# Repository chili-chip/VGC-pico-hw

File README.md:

# VGC-pico-hw
KiCad harware project for VGC-0 based on pico and esp32

Brain of the operation is RP2350, while ESP8684 is used for WiFi and extra GPIO.

Input system consists of 6 regular buttons, 2 system buttons and an encoder wheel.

Meow :3

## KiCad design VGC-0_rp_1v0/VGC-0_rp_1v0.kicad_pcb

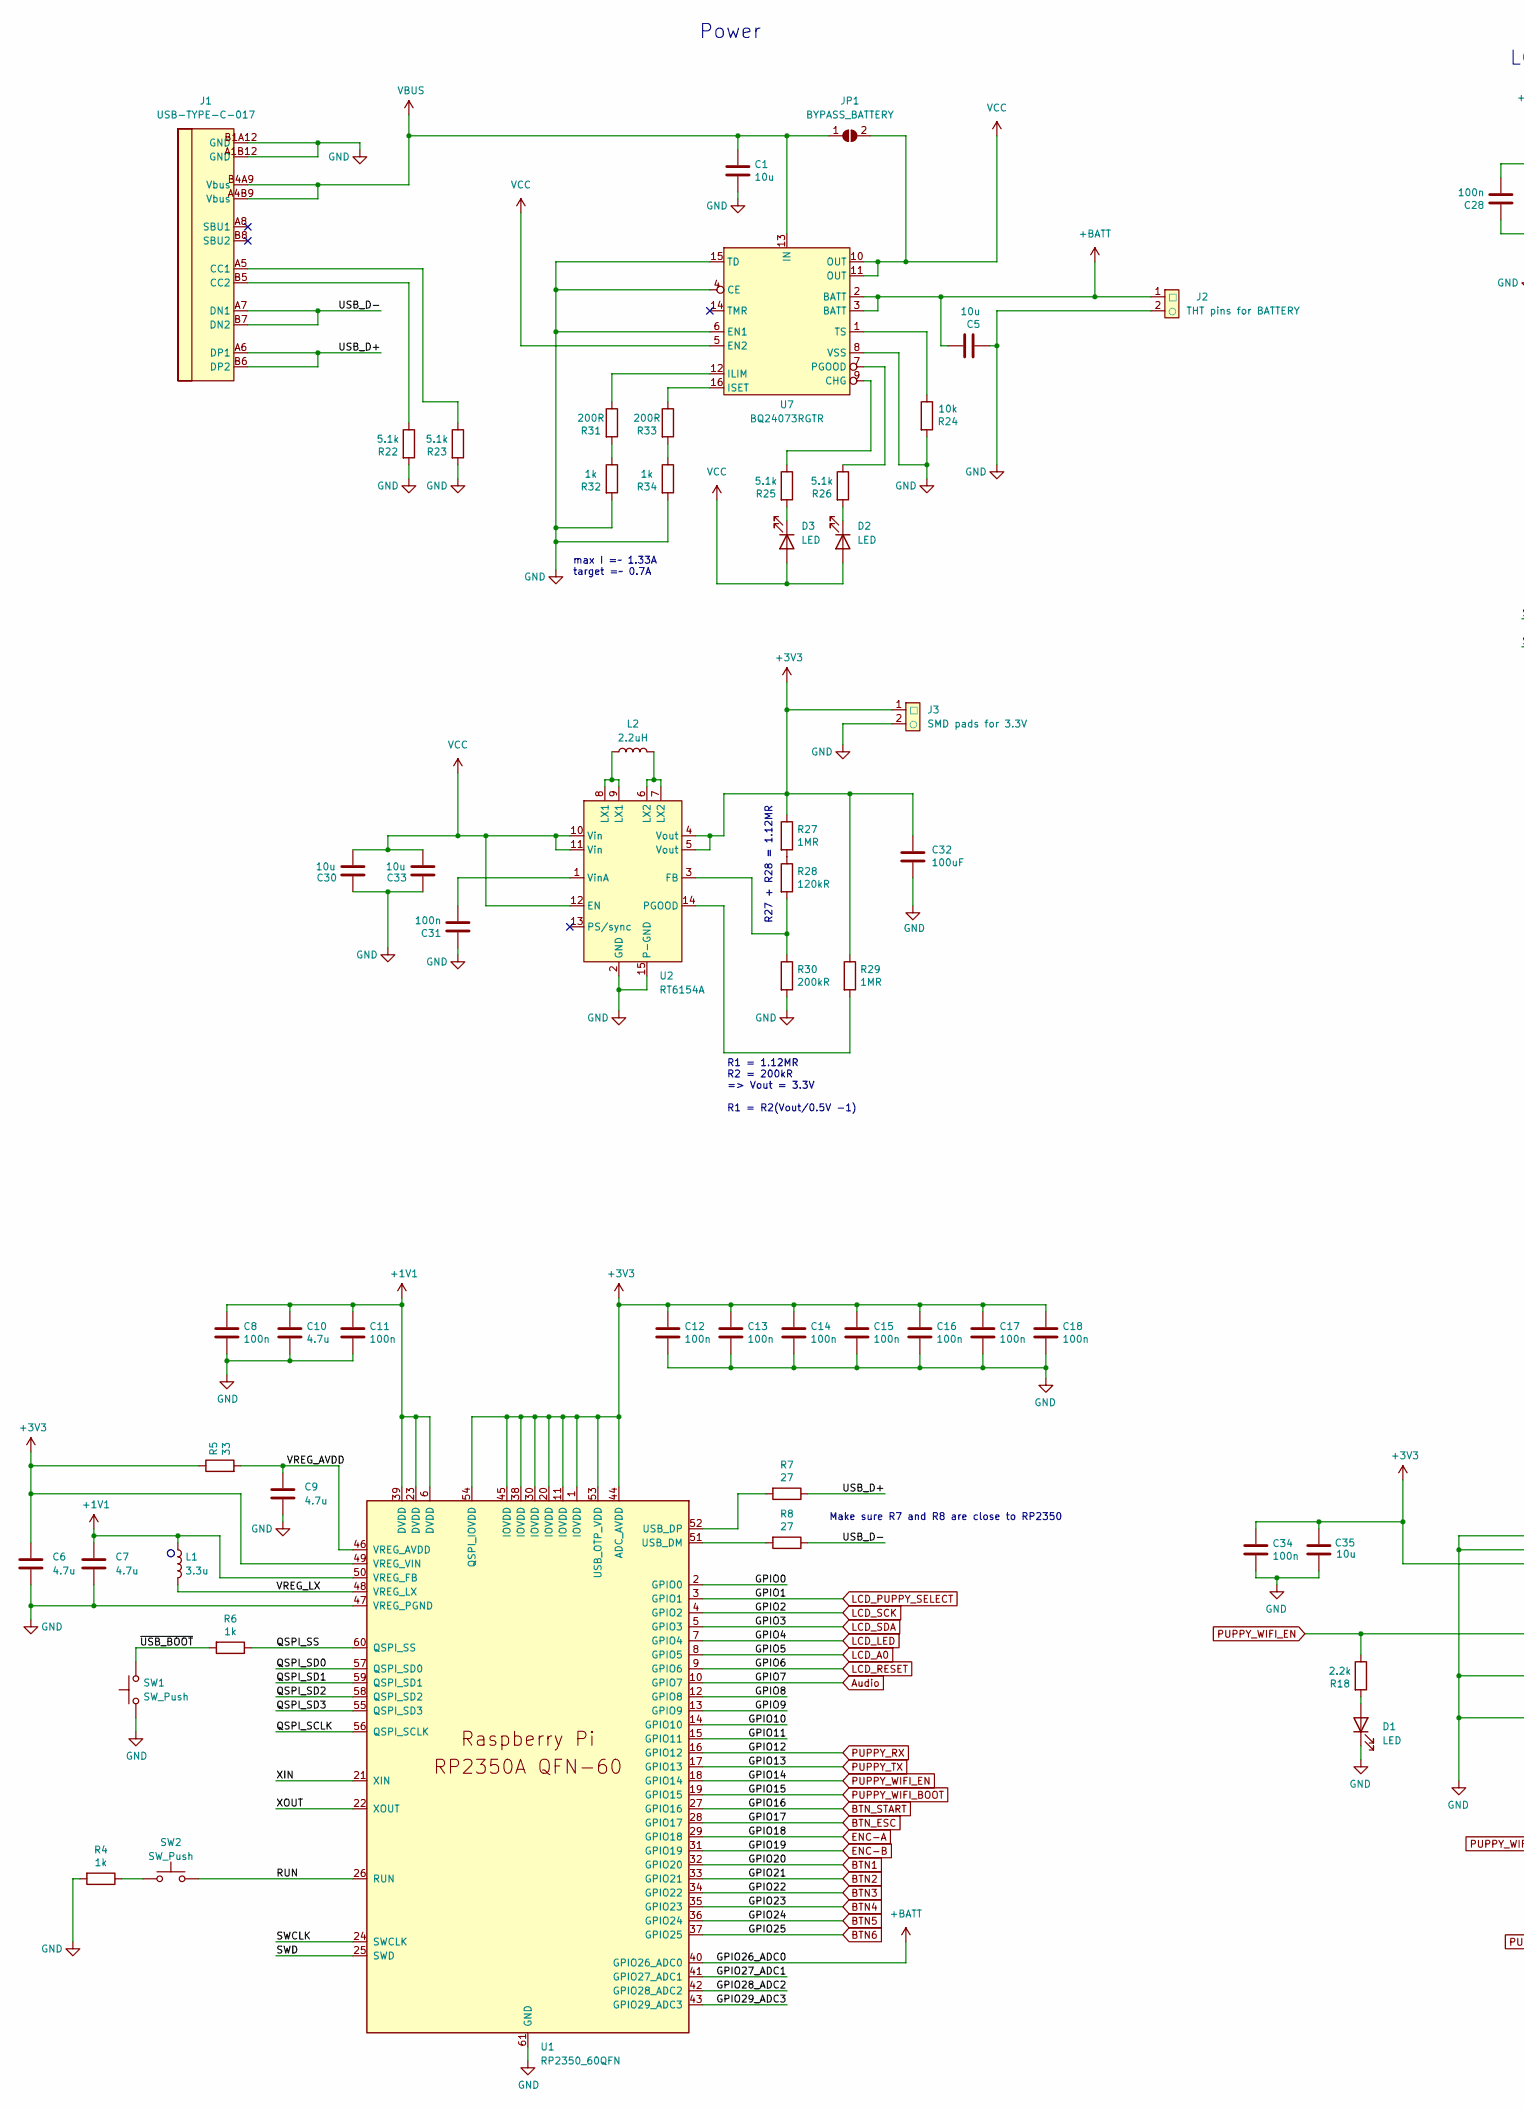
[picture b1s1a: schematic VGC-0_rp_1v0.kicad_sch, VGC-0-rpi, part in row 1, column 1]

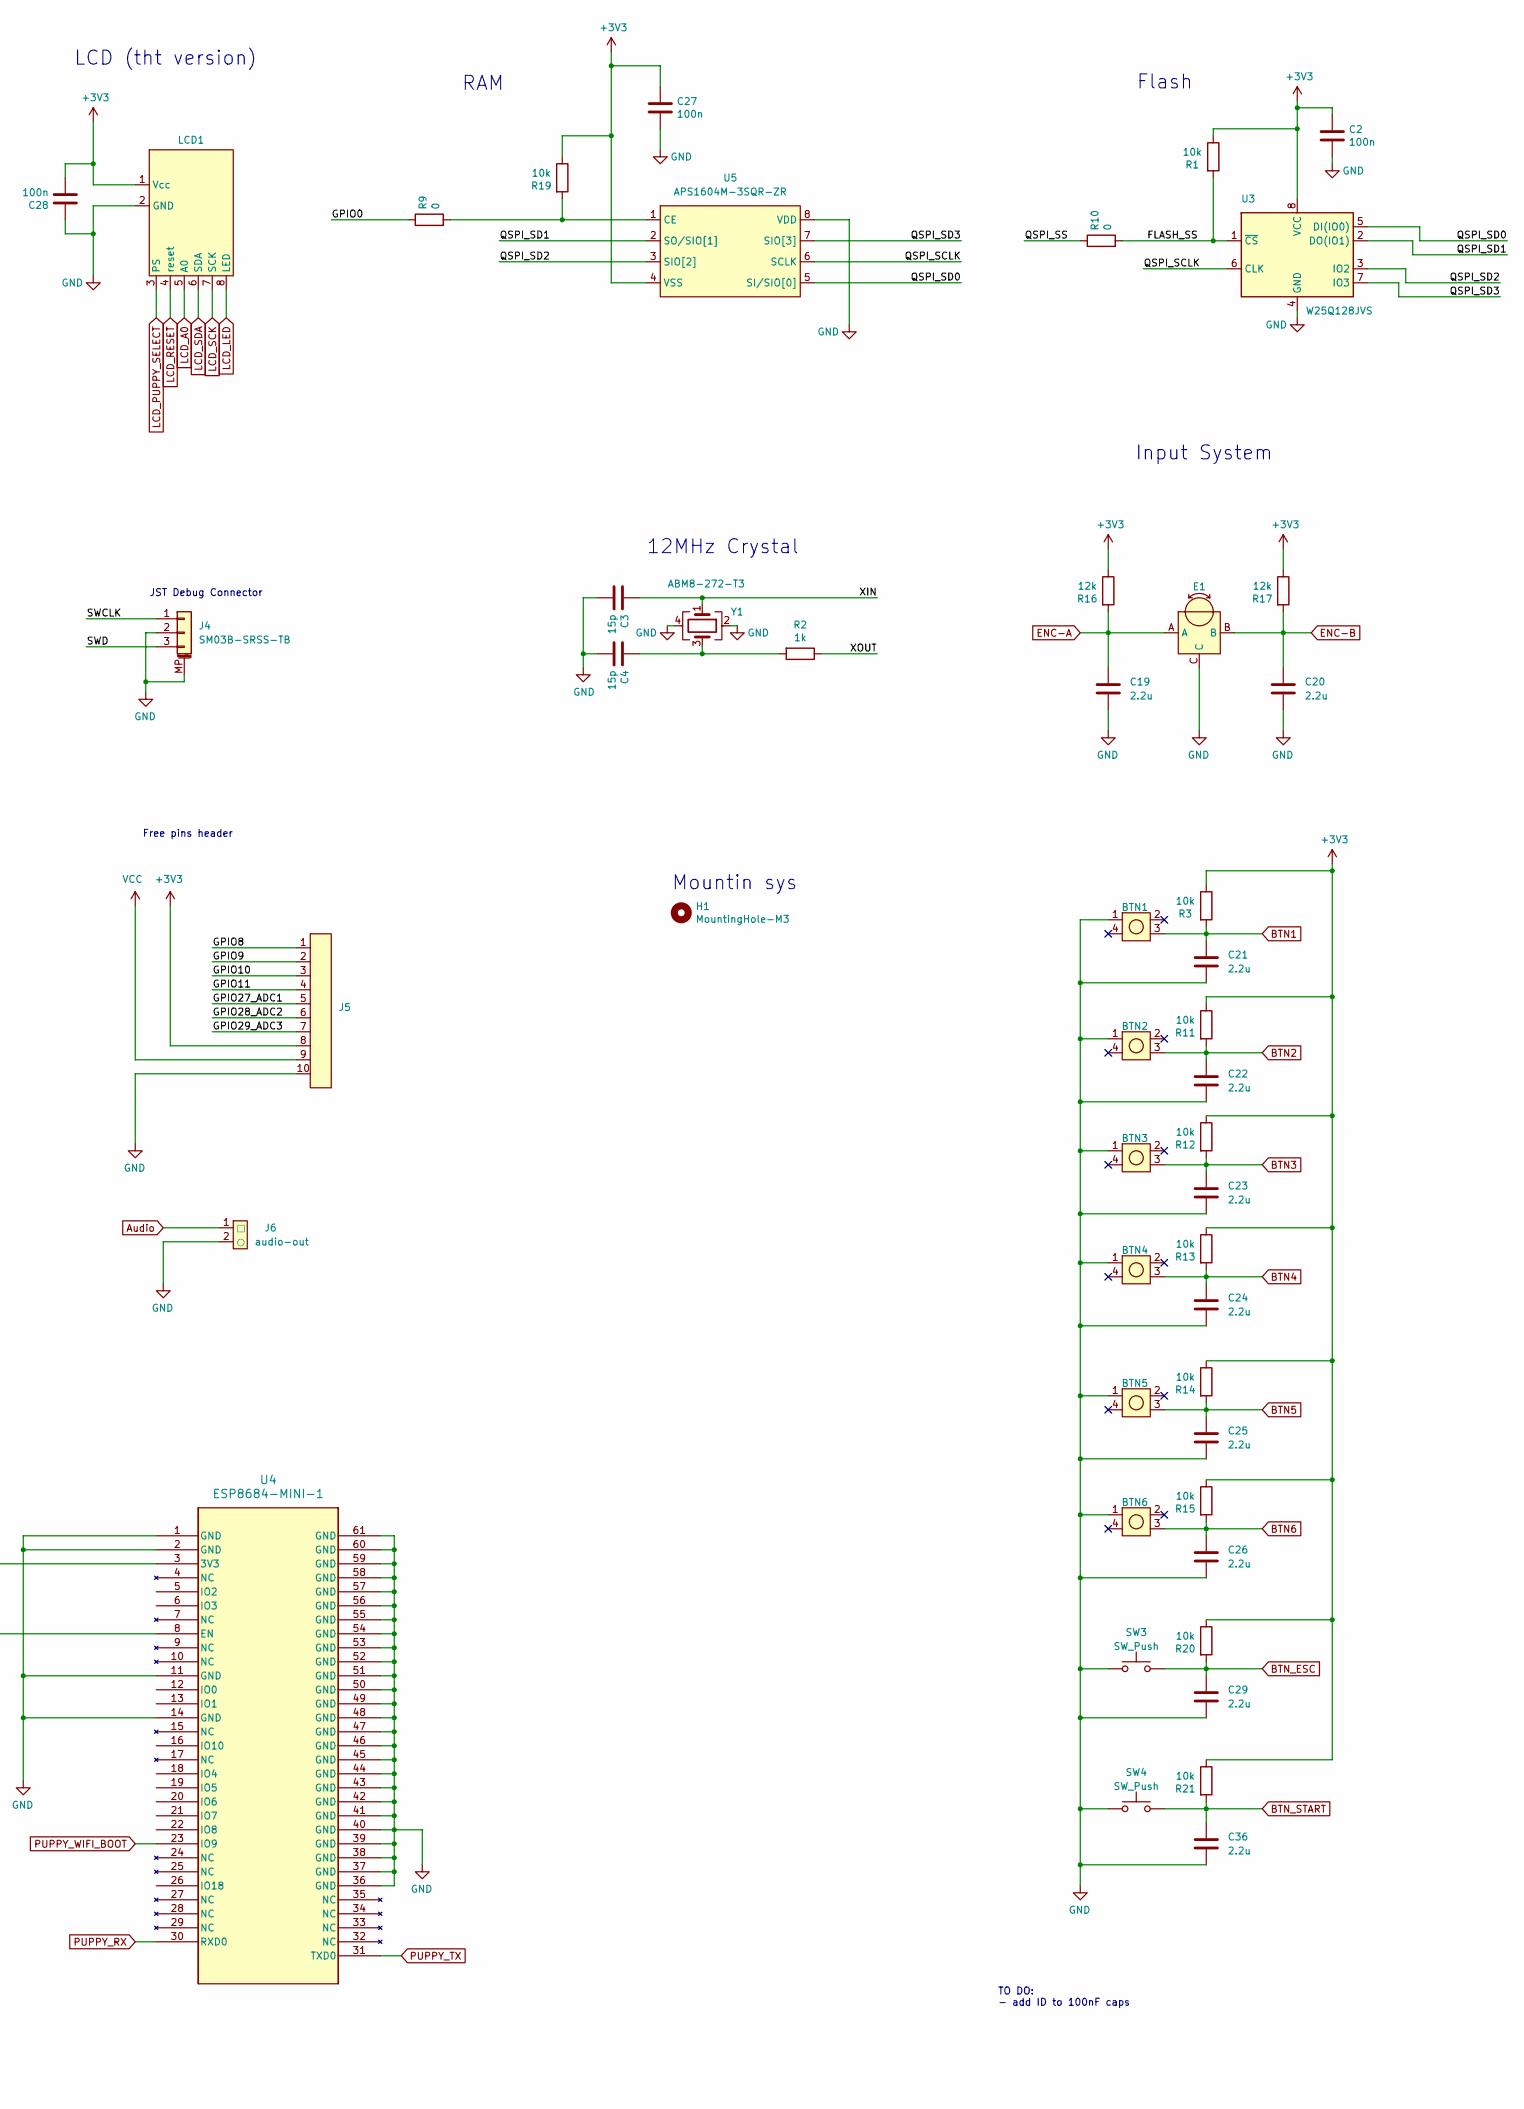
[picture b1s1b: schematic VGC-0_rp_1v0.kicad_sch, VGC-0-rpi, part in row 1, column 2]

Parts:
BTN1, BTN2, BTN3, BTN4: 8x8-tht-button
BTN5, BTN6: THT-button_2pin
C1, C5, C30, C33, C35: 10u; C_0805_2012Metric
C2, C8, C11, C12, C13, C14, C15, C16, C17, C18, C27, C28, C31, C34: 100n; C_0402_1005Metric
C3, C4: 15p; C_0402_1005Metric
C6, C7, C9: 4.7u; C_0603_1608Metric
C10: 4.7u; C_0402_1005Metric
C19, C20, C21, C22, C23, C24, C25, C26, C29, C36: 2.2u; C_0402_1005Metric
C32: 100uF; C_1206_3216Metric
D1, D2, D3: LED; D_0603_1608Metric
E1: mouse-encoder
H1: MountingHole-M3; MountingHole_3mm
J1: USB-TYPE-C-017; USB-TYPE-C-SMD_C9900008089
J2: THT pins for BATTERY; 2.54mm-2PIN
J3: SMD pads for 3.3V; SMD-solder-pad-2x
J4: SM03B-SRSS-TB; JST_SH_SM03B-SRSS-TB_1x03-1MP_P1.00mm_Horizontal
J5: 2.54mm-10PIN
J6: audio-out; 2.54mm-2PIN
JP1: BYPASS_BATTERY; SolderJumper-2_P1.3mm_Open_RoundedPad1.0x1.5mm
L1: 3.3u; L_pol_2016
L2: 2.2uH; SMD-inductor-4mm9_4mm9
LCD1: THT-SPI-LCD
R1, R3, R11, R12, R13, R14, R15, R19, R20, R21, R24: 10k; R_0402_1005Metric
R2, R4, R6, R32, R34: 1k; R_0402_1005Metric
R5: 33; R_0603_1608Metric
R7, R8: 27; R_0402_1005Metric
R9, R10: 0; R_0402_1005Metric
R16, R17: 12k; R_0402_1005Metric
R18: 2.2k; R_0402_1005Metric
R22, R23, R25, R26: 5.1k; R_0402_1005Metric
R27, R29: 1MR; R_0402_1005Metric
R28: 120kR; R_0603_1608Metric
R30: 200kR; R_0402_1005Metric
R31, R33: 200R; R_0402_1005Metric
SW1, SW2, SW3, SW4: SW_Push; SW_SPST_TL3342
U1: RP2350_60QFN; RP2350-QFN-60-1EP_7x7_P0.4mm_EP3.4x3.4mm_ThermalVias
U2: RT6154A; DFN-14-1EP_3x4mm_P0.5mm_EP1.7x3.3mm
U3: W25Q128JVS; SOIC-8_5.23x5.23mm_P1.27mm
U4: ESP8684-MINI-1
U5: APS1604M-3SQR-ZR; USON-8
U7: BQ24073RGTR; QFN-16-1EP_3x3mm_P0.5mm_EP1.7x1.7mm
Y1: ABM8-272-T3; Crystal_SMD_3225-4Pin_3.2x2.5mm

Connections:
+1V1: C7.1, C8.1, C10.1, C11.1, L1.1, U1.6 (DVDD), U1.23 (DVDD), U1.39 (DVDD), U1.50 (VREG_FB)
+3V3: C2.1, C6.1, C12.1, C13.1, C14.1, C15.1, C16.1, C17.1, C18.1, C27.1, C28.2, C32.1, C34.1, C35.1, J3.1 (□), J5.8, LCD1.1 (Vcc), R1.1, R3.1, R5.1, R11.1, R12.1, R13.1, R14.1, R15.1, R16.1, R17.1, R19.1, R20.1, R21.1, R27.1, R29.1, U1.1 (IOVDD), U1.11 (IOVDD), U1.20 (IOVDD), U1.30 (IOVDD), U1.38 (IOVDD), U1.44 (ADC_AVDD), U1.45 (IOVDD), U1.49 (VREG_VIN), U1.53 (USB_OTP_VDD), U1.54 (QSPI_IOVDD), U2.4 (Vout), U2.5 (Vout), U3.8 (VCC), U4.3 (3V3), U5.4 (VSS)
+BATT: C5.1, J2.1 (□), U1.40 (GPIO26_ADC0), U7.2 (BATT), U7.3 (BATT)
/FLASH_SS: R1.2, R10.2, U3.1 (~CS)
/GPIO0: R9.1, U1.2 (GPIO0)
/GPIO8: J5.1, U1.12 (GPIO8)
/GPIO9: J5.2, U1.13 (GPIO9)
/GPIO10: J5.3, U1.14 (GPIO10)
/GPIO11: J5.4, U1.15 (GPIO11)
/GPIO27_ADC1: J5.5, U1.41 (GPIO27_ADC1)
/GPIO28_ADC2: J5.6, U1.42 (GPIO28_ADC2)
/GPIO29_ADC3: J5.7, U1.43 (GPIO29_ADC3)
/QSPI_SCLK: U1.56 (QSPI_SCLK), U3.6 (CLK), U5.6 (SCLK)
/QSPI_SD0: U1.57 (QSPI_SD0), U3.5 (DI(IO0)), U5.5 (SI/SIO[0])
/QSPI_SD1: U1.59 (QSPI_SD1), U3.2 (DO(IO1)), U5.2 (SO/SIO[1])
/QSPI_SD2: U1.58 (QSPI_SD2), U3.3 (IO2), U5.3 (SIO[2])
/QSPI_SD3: U1.55 (QSPI_SD3), U3.7 (IO3), U5.7 (SIO[3])
/QSPI_SS: R6.1, R10.1, U1.60 (QSPI_SS)
/RUN: SW2.2, U1.26 (RUN)
/SWCLK: J4.1, U1.24 (SWCLK)
/SWD: J4.3, U1.25 (SWD)
/USB_D+: J1.A6 (DP1), J1.B6 (DP2), R7.1
/USB_D-: J1.A7 (DN1), J1.B7 (DN2), R8.1
/VREG_AVDD: C9.1, R5.2, U1.46 (VREG_AVDD)
/VREG_LX: L1.2, U1.48 (VREG_LX)
/XIN: C3.1, U1.21 (XIN), Y1.1
/XOUT: R2.1, U1.22 (XOUT)
/~USB_BOOT: R6.2, SW1.2
Audio: J6.1 (□), U1.10 (GPIO7)
BTN1: BTN1.3, C21.1, R3.2, U1.32 (GPIO20)
BTN2: BTN2.3, C22.1, R11.2, U1.33 (GPIO21)
BTN3: BTN3.3, C23.1, R12.2, U1.34 (GPIO22)
BTN4: BTN4.3, C24.1, R13.2, U1.35 (GPIO23)
BTN5: BTN5.3, C25.1, R14.2, U1.36 (GPIO24)
BTN6: BTN6.3, C26.1, R15.2, U1.37 (GPIO25)
BTN_ESC: C29.1, R20.2, SW3.2, U1.28 (GPIO17)
BTN_START: C36.1, R21.2, SW4.2, U1.27 (GPIO16)
ENC-A: C19.1, E1.A, R16.2, U1.29 (GPIO18)
ENC-B: C20.1, E1.B, R17.2, U1.31 (GPIO19)
GND: BTN1.1, BTN2.1, BTN3.1, BTN4.1, BTN5.1, BTN6.1, C1.2, C2.2, C3.2, C4.2, C5.2, C6.2, C7.2, C8.2, C9.2, C10.2, C11.2, C12.2, C13.2, C14.2, C15.2, C16.2, C17.2, C18.2, C19.2, C20.2, C21.2, C22.2, C23.2, C24.2, C25.2, C26.2, C27.2, C28.1, C29.2, C30.1, C31.1, C32.2, C33.1, C34.2, C35.2, C36.2, D1.1 (K), E1.C, J1.A1B12 (GND), J1.B1A12 (GND), J2.2 (○), J3.2 (○), J4.2, J4.MP (MountPin), J5.10, J6.2 (○), LCD1.2 (GND), R4.2, R22.2, R23.2, R24.2, R30.2, R32.2, R34.2, SW1.1, SW3.1, SW4.1, U1.47 (VREG_PGND), U1.61 (GND), U2.2 (GND), U2.15 (P-GND), U3.4 (GND), U4.1 (GND), U4.2 (GND), U4.11 (GND), U4.14 (GND), U4.36 (GND), U4.37 (GND), U4.38 (GND), U4.39 (GND), U4.40 (GND), U4.41 (GND), U4.42 (GND), U4.43 (GND), U4.44 (GND), U4.45 (GND), U4.46 (GND), U4.47 (GND), U4.48 (GND), U4.49 (GND), U4.50 (GND), U4.51 (GND), U4.52 (GND), U4.53 (GND), U4.54 (GND), U4.55 (GND), U4.56 (GND), U4.57 (GND), U4.58 (GND), U4.59 (GND), U4.60 (GND), U4.61 (GND), U5.8 (VDD), U7.4 (CE), U7.6 (EN1), U7.8 (VSS), U7.15 (TD), Y1.2, Y1.4
LCD_A0: LCD1.5 (A0), U1.8 (GPIO5)
LCD_LED: LCD1.8 (LED), U1.7 (GPIO4)
LCD_PUPPY_SELECT: LCD1.3 (PS), U1.3 (GPIO1)
LCD_RESET: LCD1.4 (reset), U1.9 (GPIO6)
LCD_SCK: LCD1.7 (SCK), U1.4 (GPIO2)
LCD_SDA: LCD1.6 (SDA), U1.5 (GPIO3)
unnamed: C4.1, R2.2, Y1.3
unnamed: D1.2 (A), R18.2
unnamed: D2.1 (K), R26.2
unnamed: D3.1 (K), R25.2
unnamed: J1.A5 (CC1), R23.1
unnamed: J1.B5 (CC2), R22.1
unnamed: L2.1, U2.8 (LX1), U2.9 (LX1)
unnamed: L2.2, U2.6 (LX2), U2.7 (LX2)
unnamed: R4.1, SW2.1
unnamed: R27.2, R28.1
unnamed: R31.2, R32.1
unnamed: R33.2, R34.1
unnamed: R8.2, U1.51 (USB_DM)
unnamed: R7.2, U1.52 (USB_DP)
unnamed: R28.2, R30.1, U2.3 (FB)
unnamed: R29.2, U2.14 (PGOOD)
unnamed: C31.2, U2.1 (VinA)
unnamed: R9.2, R19.2, U5.1 (CE)
unnamed: R25.1, U7.9 (CHG)
unnamed: R31.1, U7.12 (ILIM)
unnamed: R33.1, U7.16 (ISET)
unnamed: R26.1, U7.7 (PGOOD)
unnamed: R24.1, U7.1 (TS)
PUPPY_RX: U1.16 (GPIO12), U4.30 (RXD0)
PUPPY_TX: U1.17 (GPIO13), U4.31 (TXD0)
PUPPY_WIFI_BOOT: U1.19 (GPIO15), U4.23 (IO9)
PUPPY_WIFI_EN: R18.1, U1.18 (GPIO14), U4.8 (EN)
VBUS: C1.1, J1.A4B9 (Vbus), J1.B4A9 (Vbus), JP1.1 (A), U7.13 (IN)
VCC: C30.2, C33.2, D2.2 (A), D3.2 (A), J5.9, JP1.2 (B), U2.10 (Vin), U2.11 (Vin), U2.12 (EN), U7.5 (EN2), U7.10 (OUT), U7.11 (OUT)

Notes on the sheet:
JST Debug Connector
LCD (tht version)
RAM
R1 = 1.12MR R2 = 200kR => Vout = 3.3V R1 = R2(Vout/0.5V -1)
Mountin sys
Input System
Flash
Make sure R7 and R8 are close to RP2350
Free pins header
max I =~ 1.33A target =~ 0.7A
12MHz Crystal
R27 + R28 = 1.12MR
Power
TO DO: - add ID to 100nF caps

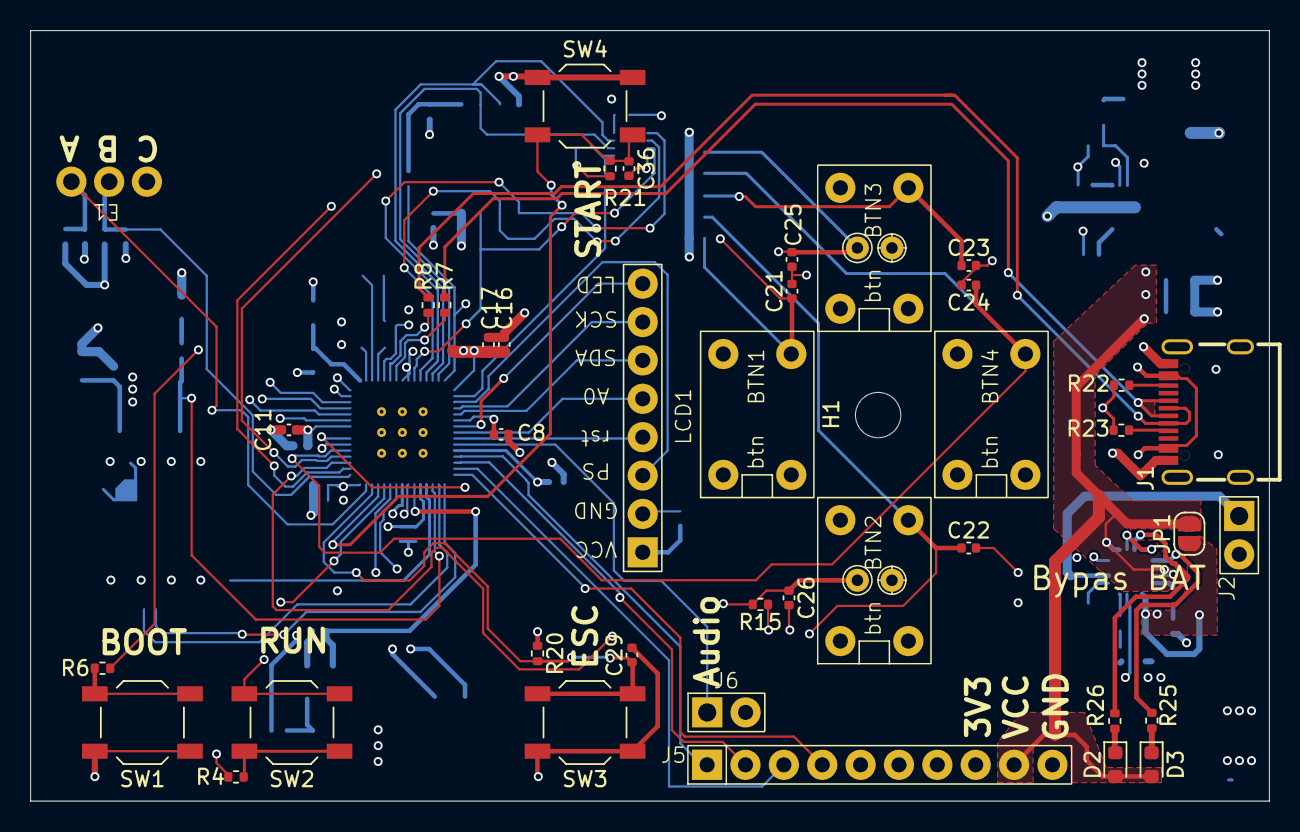
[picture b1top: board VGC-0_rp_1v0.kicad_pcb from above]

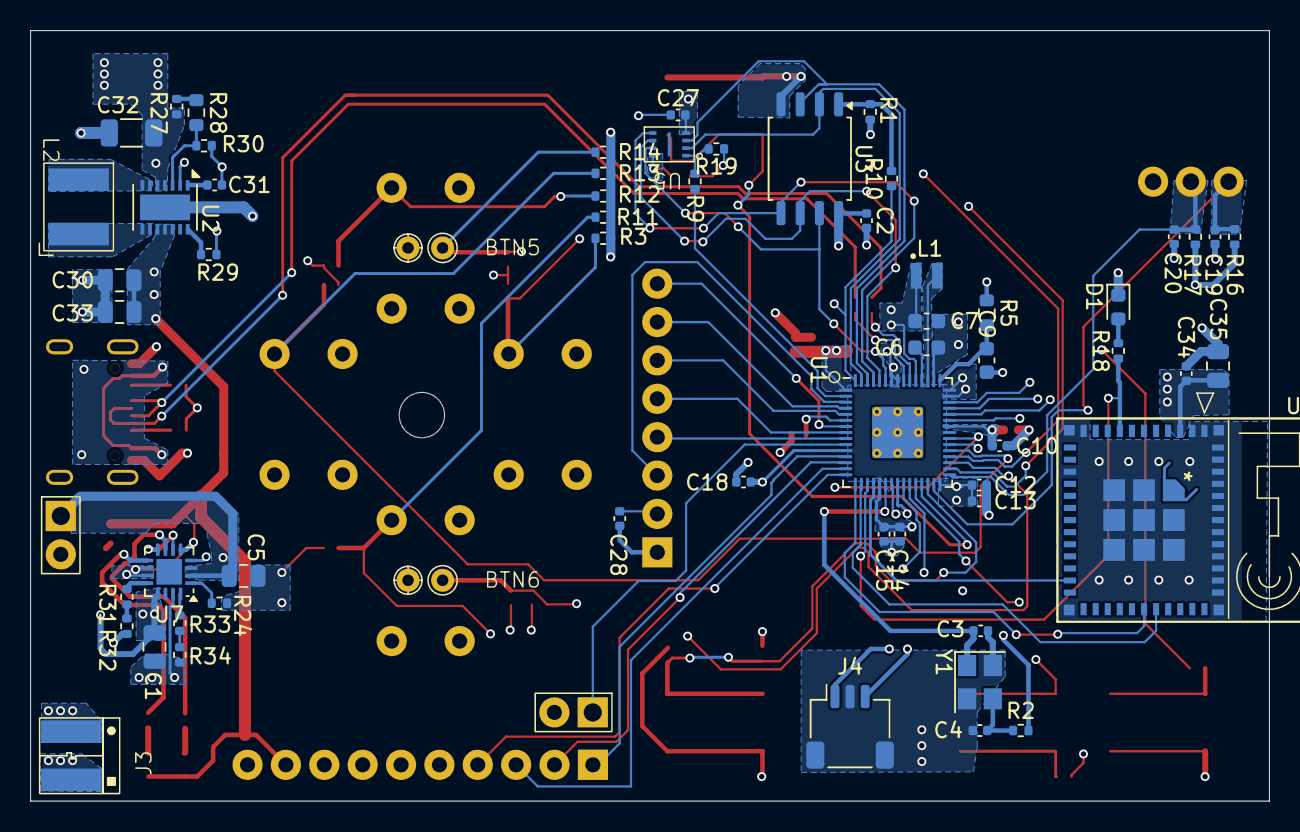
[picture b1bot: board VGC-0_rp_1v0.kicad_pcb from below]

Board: 4 copper layers, 82.0 x 51.0 mm, 102 parts (61 on the bottom side), 75 nets.

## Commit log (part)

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2025-08-06 inital commit
2025-08-07 power sys update 0
